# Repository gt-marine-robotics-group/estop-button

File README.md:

# Emergency Stop Button

The emergency stop button is used on our surface vehicles, such as the WAM-V.

## System Schematic

## Design History

### v1.0r0
Designers: Concept - Will Sonnleitner, Ryan Su, Sean Fish; Schematic - Ryan Su, Sean Fish; PCB - Ryan Su, Sean Fish

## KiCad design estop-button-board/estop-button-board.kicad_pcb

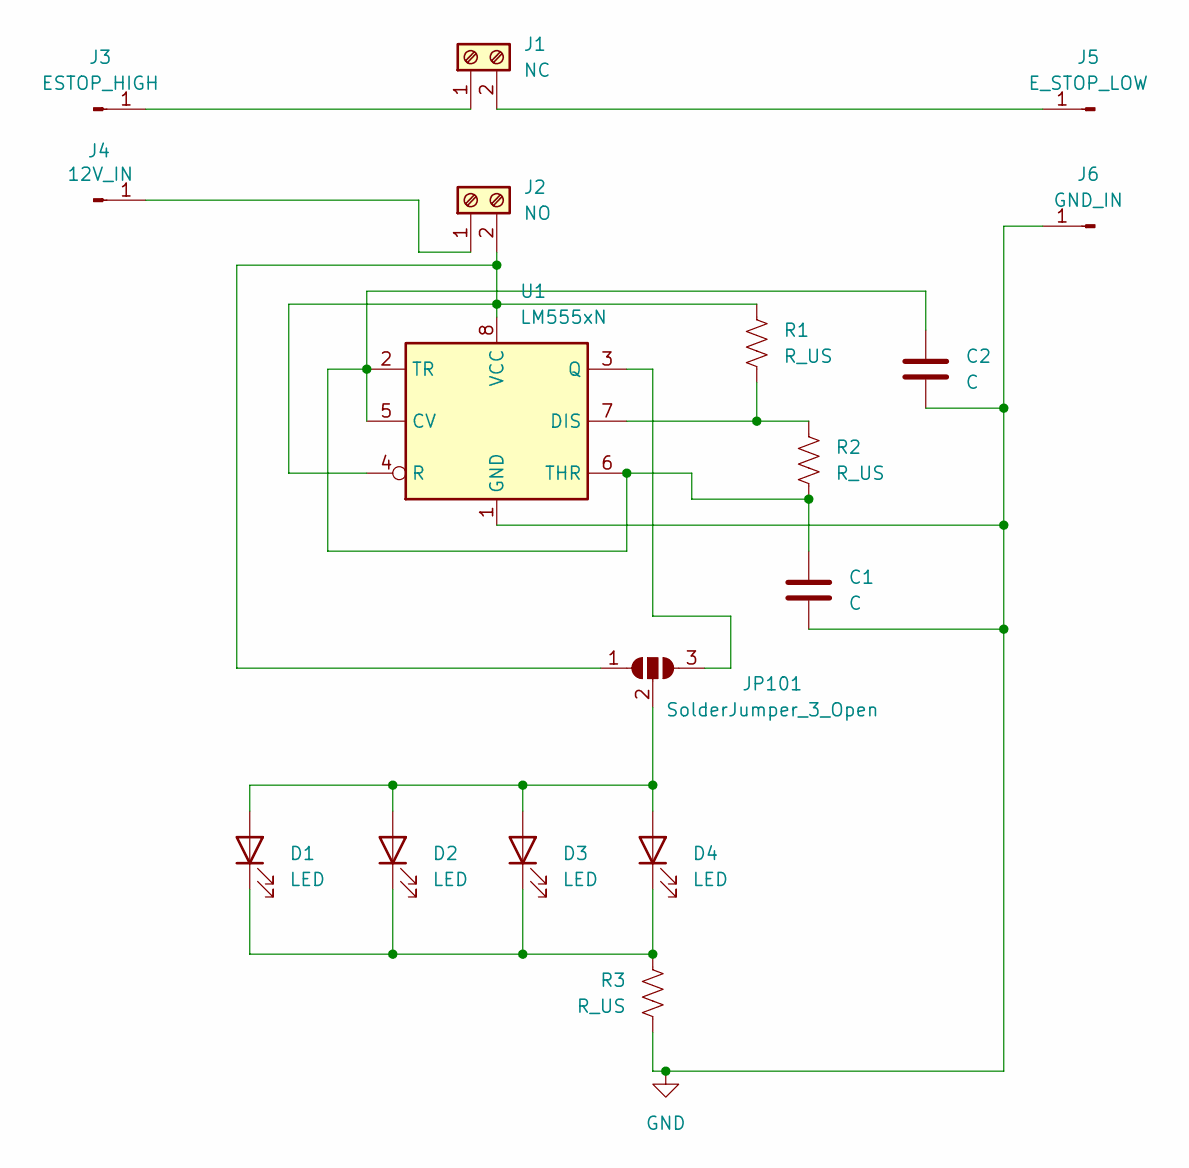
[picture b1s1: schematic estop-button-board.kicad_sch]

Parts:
C1: C; CP_Radial_D4.0mm_P2.00mm
C2: C; C_0603_1608Metric_Pad1.08x0.95mm_HandSolder
D1, D2, D3, D4: LED; LED_D3.0mm
J1: NC; SolderWire-0.5sqmm_1x02_P4.6mm_D0.9mm_OD2.1mm
J2: NO; SolderWire-0.5sqmm_1x02_P4.6mm_D0.9mm_OD2.1mm
J3: ESTOP_HIGH; SolderWire-0.5sqmm_1x01_D0.9mm_OD2.1mm
J4: 12V_IN; SolderWire-0.5sqmm_1x01_D0.9mm_OD2.1mm
J5: E_STOP_LOW; SolderWire-0.5sqmm_1x01_D0.9mm_OD2.1mm
J6: GND_IN; SolderWire-0.5sqmm_1x01_D0.9mm_OD2.1mm
JP101: SolderJumper_3_Open; SolderJumper-3_P1.3mm_Open_Pad1.0x1.5mm
R1, R2, R3: R_US; R_0805_2012Metric_Pad1.20x1.40mm_HandSolder
U1: LM555xN; DIP-8_W7.62mm

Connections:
GND: C1.2, C2.2, J6.1, R3.2, U1.1 (GND)
unnamed: D1.2 (A), D2.2 (A), D3.2 (A), D4.2 (A), JP101.2 (C)
unnamed: D1.1 (K), D2.1 (K), D3.1 (K), D4.1 (K), R3.1
unnamed: J1.1, J3.1
unnamed: J1.2, J5.1
unnamed: J2.1, J4.1
unnamed: J2.2, JP101.1 (A), R1.2, U1.4 (R), U1.8 (VCC)
unnamed: JP101.3 (B), U1.3 (Q)
unnamed: C1.1, C2.1, R2.1, U1.2 (TR), U1.5 (CV), U1.6 (THR)
unnamed: R1.1, R2.2, U1.7 (DIS)

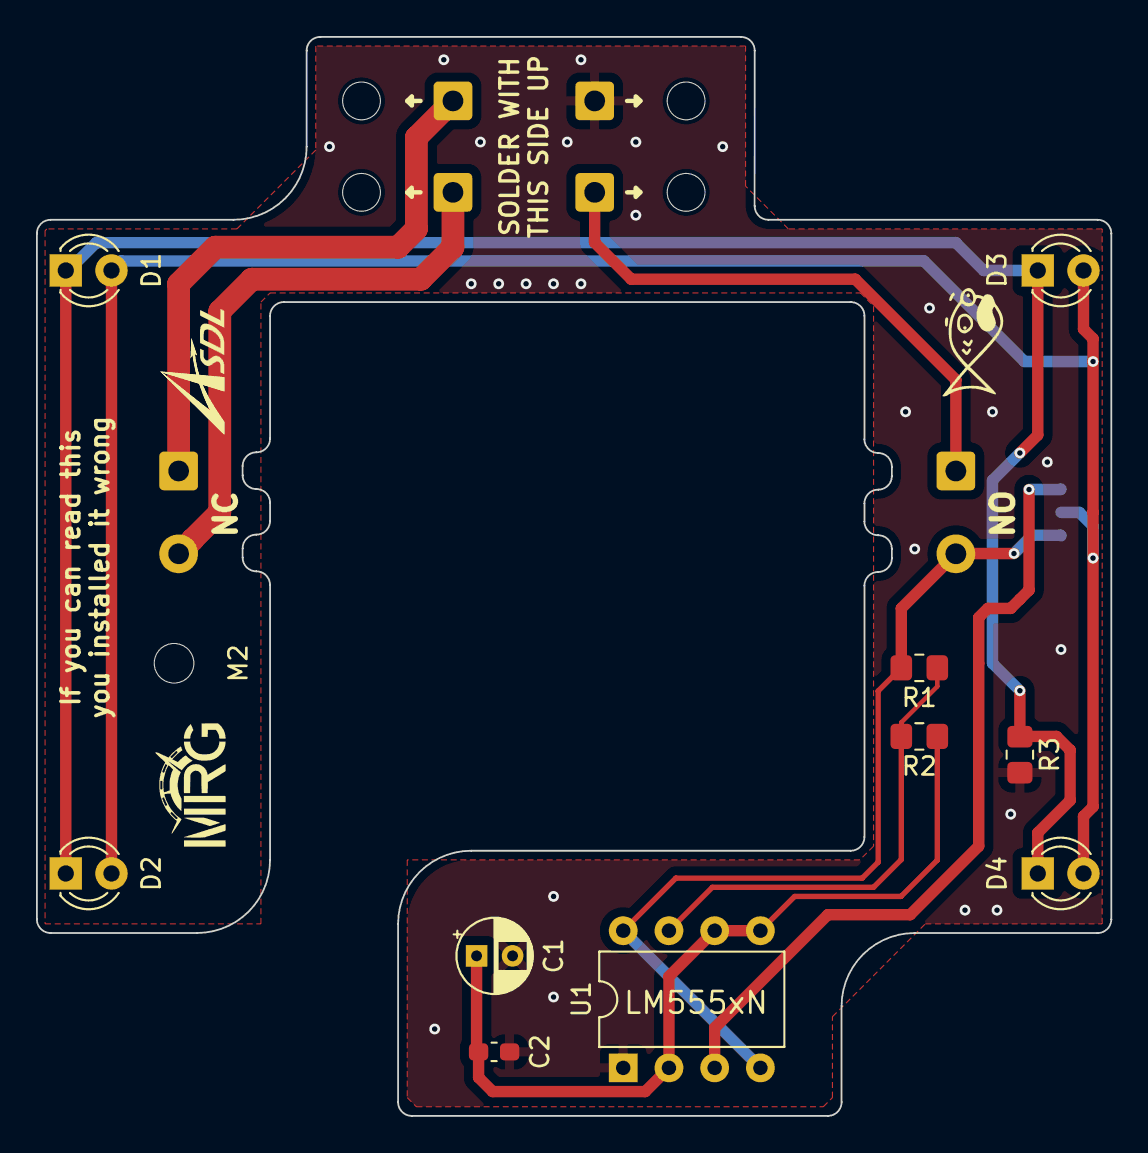
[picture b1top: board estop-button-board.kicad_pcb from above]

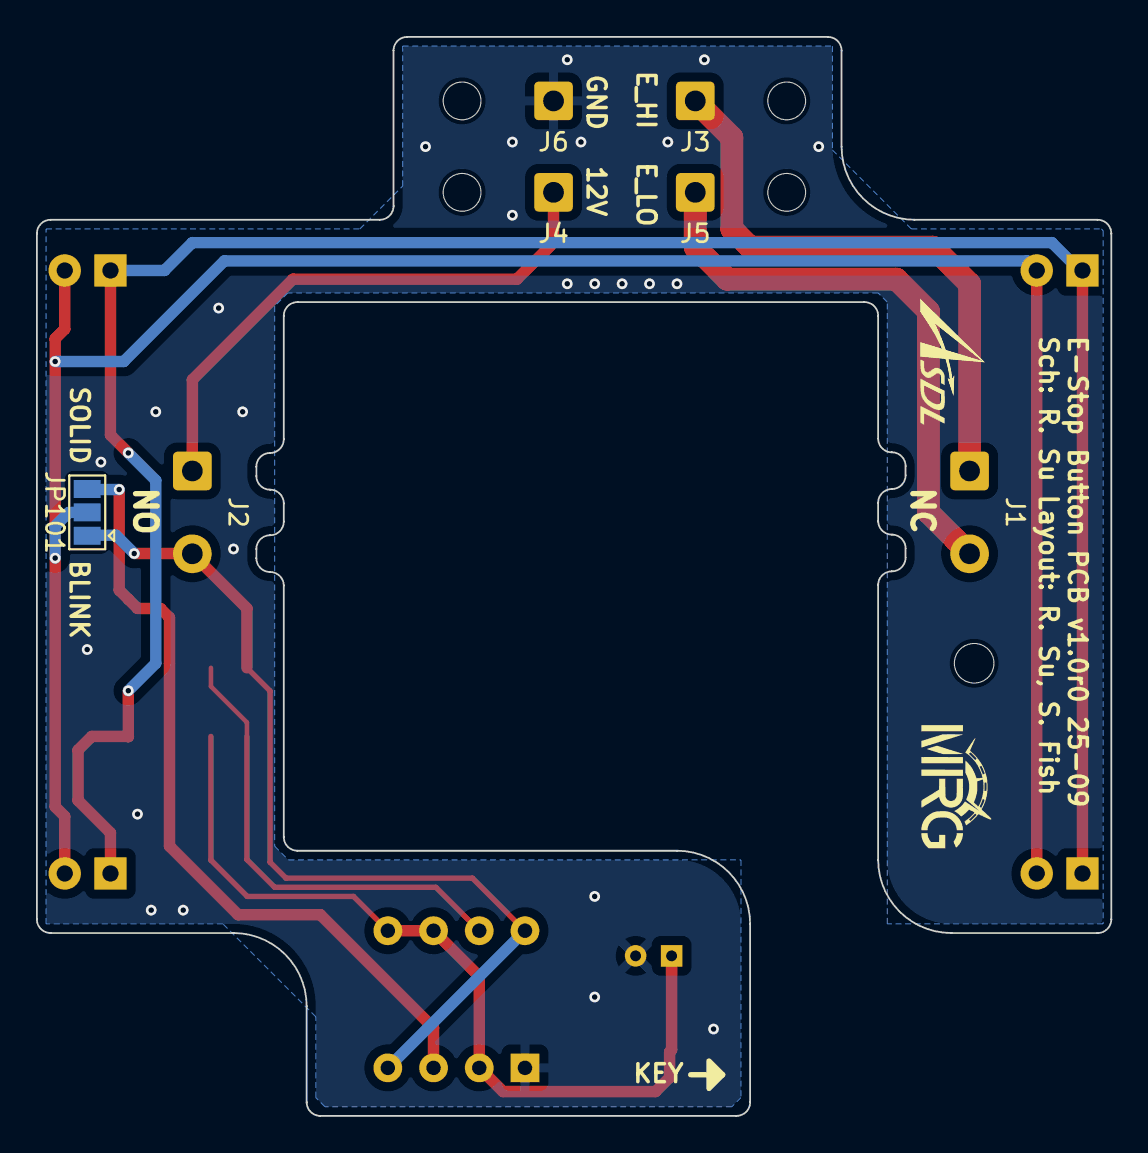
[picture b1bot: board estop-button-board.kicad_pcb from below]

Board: 2 copper layers, 59.7 x 59.9 mm, 18 parts (5 on the bottom side), 10 nets.

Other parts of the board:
M2: MountingHole_2.2mm_M2

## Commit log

2025-09-30 Added kicad files
